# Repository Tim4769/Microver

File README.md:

# Microver

Microver is a compact rover built for the Swiss Rover Challenge. This repository collects the project's electronics, mechanical CAD, software scaffold, PCB test firmware, photos, and shared assets in one place.

## Project

- **Competition:** Swiss Rover Challenge, Switzerland's rover competition for teams of 5 high school students.
- **2025 result:** 3rd place.
- **2026 result:** 1st place.
- **Main disciplines:** electronics, mechanical design, and software.

## Start Here

| Area | Path | Contents |
|---|---|---|
| Electronics | `hardware/final/README.md` | Active PCB revisions, KiCad projects, manufacturing outputs, and validation notes. |
| Mechanical | `mechanical/README.md` | Rover assemblies, wheel pods, chassis parts, mechanisms, mounts, and STEP exports. |
| Software | `software/` | Python rover-control scaffold with camera and control services. |
| PCB test firmware | `hardware/pcb_testing_firmware/README.md` | Arduino sketches and docs for board bring-up and electronics validation. |
| Power diagrams | `hardware/flow_charts/README.md` | Power-system flow charts and supporting diagrams. |

## Current Snapshot

**Electronics**
- Manufacturing-ready PCB work is under `hardware/final/`; archived board spins live under `hardware/archive/`.
- The active stack covers protection Rev B, boost Rev C, buck Rev C, high-side OR-ing Rev A, compute Rev A, and final control Rev A.

**Mechanical**
- Modular CAD lives in `mechanical/assemblies/` and `mechanical/components/`.
- The rover uses field-serviceable wheel pods, aluminium extrusion rails, custom 3D-printed parts, and integrated mounts for electronics, sensors, and mechanisms.

**Software**
- `software/` is the autonomy-ready rover software workspace for control, camera, perception, navigation, and system integration.
- `hardware/pcb_testing_firmware/` contains electronics bring-up and validation sketches only; it is separate from the final software stack.

## Repository Map

- `hardware/` - PCB designs, manufacturing files, archived board revisions, power diagrams, and PCB validation firmware.
- `mechanical/` - CAD assemblies, exported STEP components, manufacturing notes, and mechanical integration references.
- `software/` - Raspberry Pi control software scaffold and future rover software workspace.
- `photos/` - Build, test, and competition photos.
- `logo/` - Current and legacy logo assets.
- `jingle/` - Project audio assets.
- `Microver_presentation_final.pdf` - Final presentation and system overview.

## Maintenance Notes

- Keep generated PCB outputs inside the relevant board revision folder.
- Update CAD references when board dimensions, connector orientation, sensor placement, or mounting details change.
- Keep editable CAD, exported review files, and assembly notes together.
- Keep PCB validation sketches separate from final rover software.
- Update this README when top-level folders move or new subsystem entry points are added.

## License / Contact

All rights reserved. No permission is granted to use, copy, modify, or distribute this repository or its contents without prior written consent. See `LICENSE` for exact terms.

Contact: Tim Wang - timwang007@outlook.com.

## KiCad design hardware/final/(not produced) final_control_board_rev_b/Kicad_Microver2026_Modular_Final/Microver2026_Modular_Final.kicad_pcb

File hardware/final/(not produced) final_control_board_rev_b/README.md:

# Final Control Board - Rev B (Not Produced)

**Revision:** Rev B  
**Production status:** Not produced / not fabricated  
**Project:** Project CK

## Photo
**Note:** Rev B was not produced or fabricated. This photo shows the complete Rev A hardware stack, with every board assembled together—not only the final control board—and is included for visual reference only.

## 1) Overview
This folder contains the KiCad source for an unproduced Rev B update of the Microver 2026 final control board.

The main correction in this KiCad project is that the second motor-driver output net issue from Rev A has been resolved: the connection intended for `OUTA` is no longer tied to the `OUTB` net.

## 2) Important compatibility note
Rev B keeps the same motor-driver stage as Rev A. Because of that, this design is still not compatible with connecting the motor-driver supply directly to the 36 V output from the boost converter.

Do not fabricate or use this design as-is for a 36 V boosted motor rail. If this design is used as the starting point for a future control board, the motor-driver stage should be redesigned with a driver/controller that is suitable for the intended boosted motor voltage. Possible examples include:

- `MP6613`
- `DRV8840`

The final driver selection should be checked against the required motor voltage, current, thermal limits, package, PCB layout constraints, and control-interface requirements before production.

## 3) Files in this folder
- `Kicad_Microver2026_Modular_Final/` - KiCad source project for the unproduced Rev B control board.
- `Photo.JPG` - Complete Rev A board-assembly photo, included only as a visual reference because Rev B was not produced.

Regenerate and review all manufacturing outputs, BOM, CPL, and design-rule checks before considering any future fabrication.

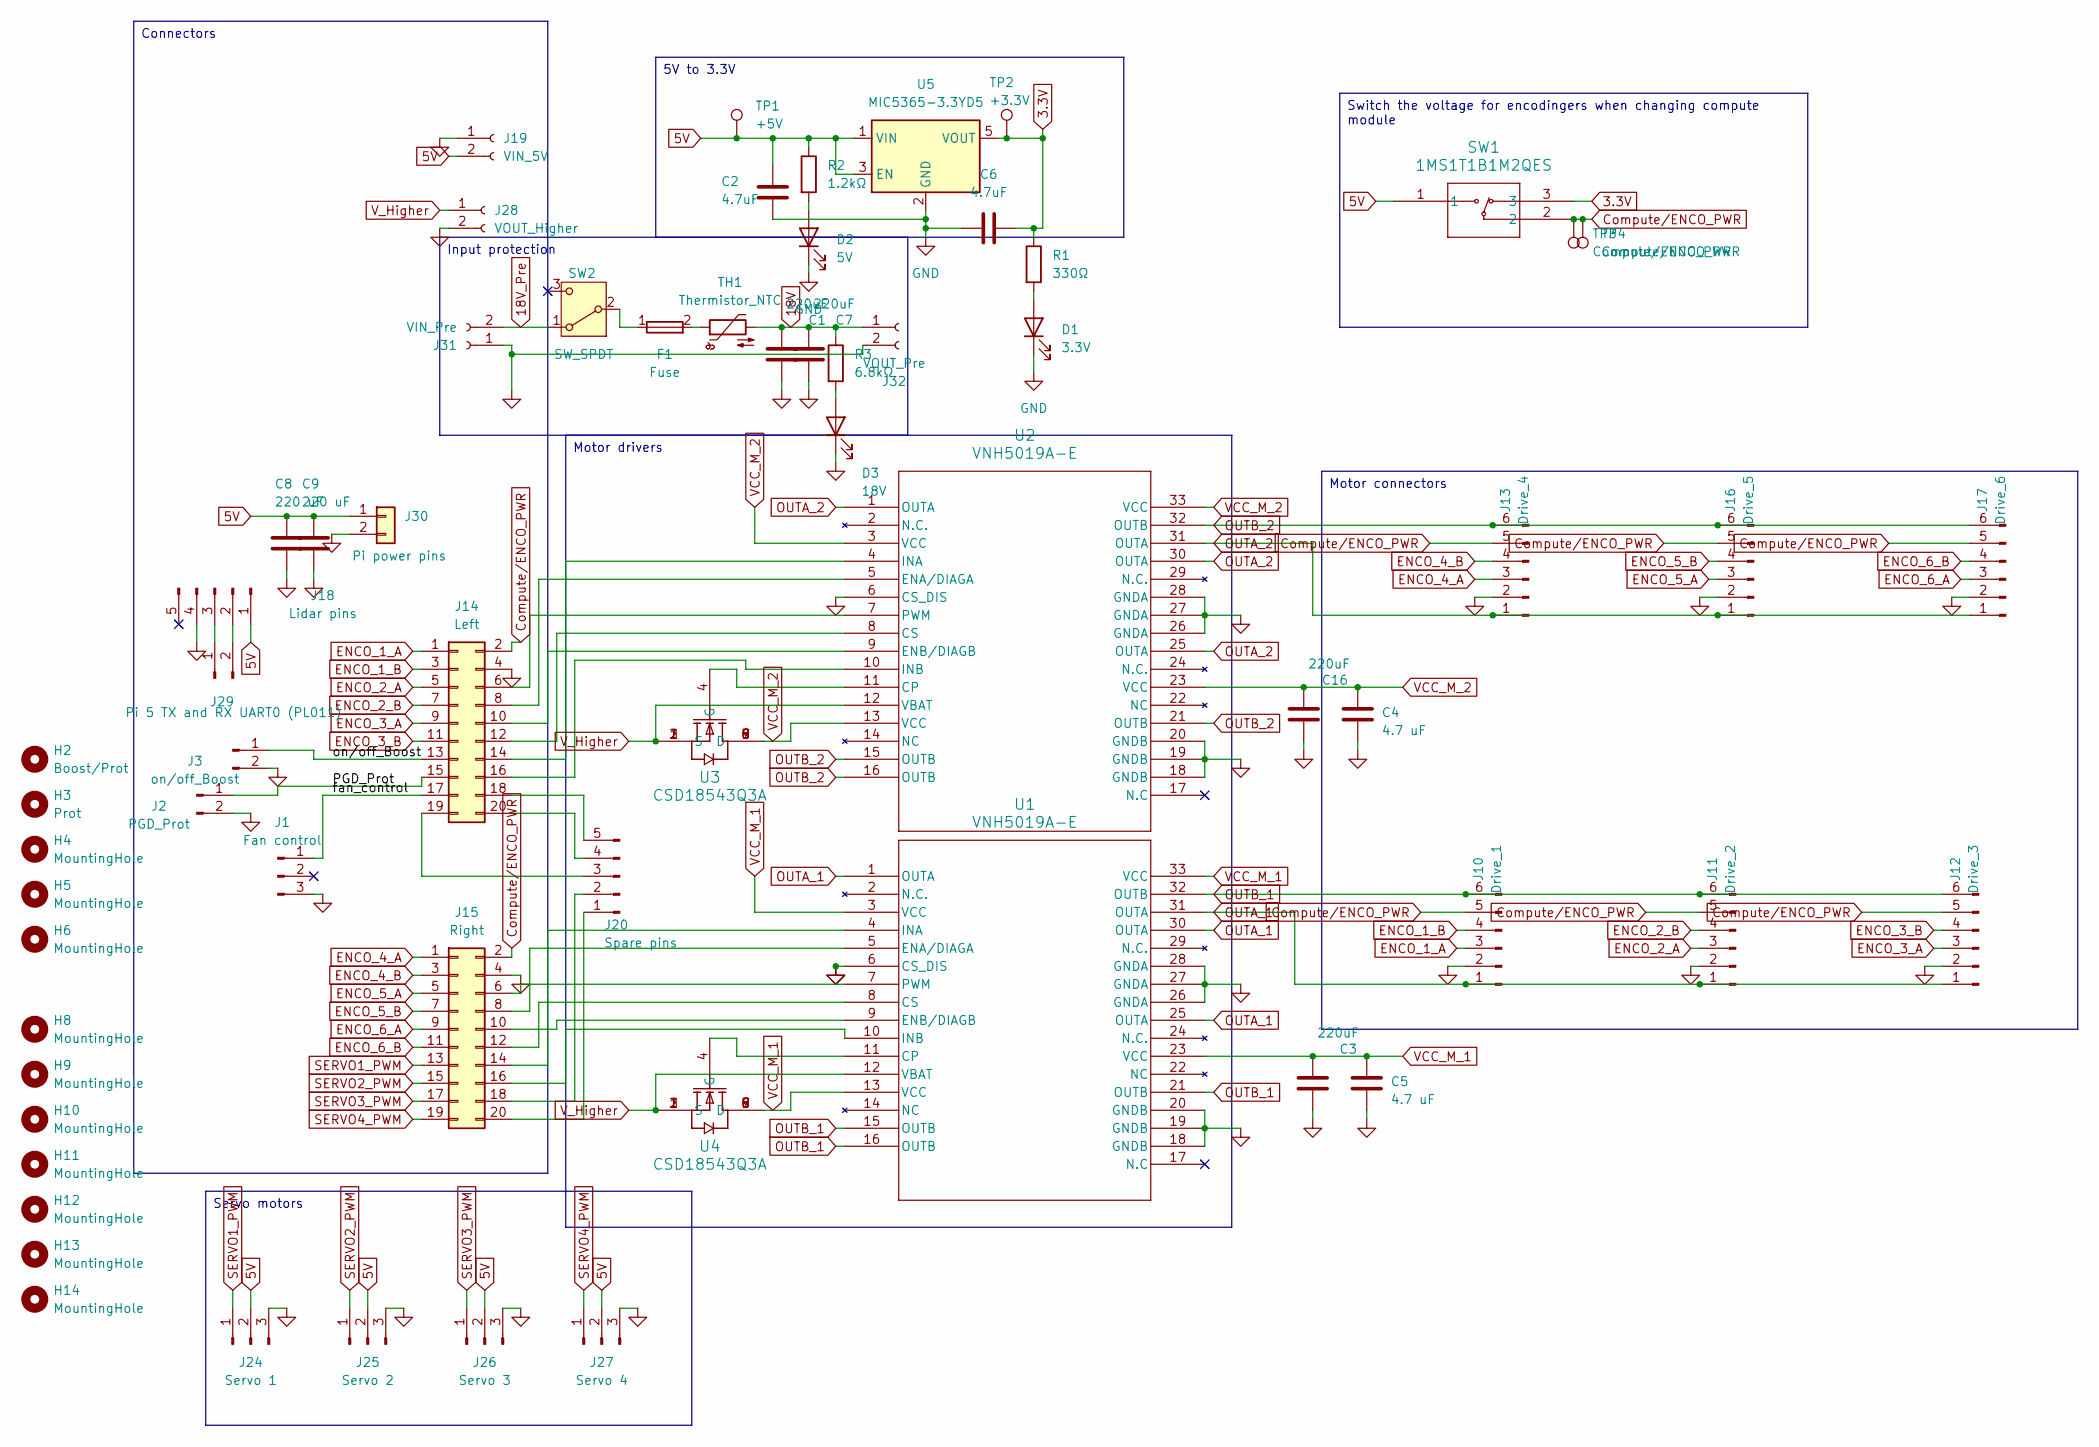
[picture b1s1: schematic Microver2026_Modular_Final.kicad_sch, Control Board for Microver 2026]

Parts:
C1, C3, C7, C16: 220uF; CP_Radial_D8.0mm_P3.50mm; JLCPCB Part Number C106697
C2, C6: 4.7uF; C_0603_1608Metric; JLCPCB Part Number C19666
C4, C5: 4.7 uF; C_1206_3216Metric; JLCPCB Part Number C29823
C8, C9: 220 uF; CP_Elec_4x5.4; JLCPCB Part Number C116389
D1: 3.3V; LED_0603_1608Metric; JLCPCB Part Number C126319
D2: 5V; LED_0603_1608Metric; JLCPCB Part Number C22371297
D3: 18V; LED_0603_1608Metric; JLCPCB Part Number C22371297
F1: Fuse; Fuse PTF-77; JLCPCB Part Number C717030
H2: Boost/Prot; MountingHole_3.2mm_M3
H3: Prot; MountingHole_3.2mm_M3
H4, H5, H6, H8, H9, H10, H11, H12, H13, H14: MountingHole; MountingHole_3.2mm_M3
J1: Fan control; PinHeader_1x03_P2.54mm_Vertical; JLCPCB Part Number C2937625
J2: PGD_Prot; PinHeader_1x02_P2.54mm_Vertical; JLCPCB Part Number C492401
J3: on/off_Boost; PinHeader_1x02_P2.54mm_Vertical; JLCPCB Part Number C492401
J10: Drive_1; JST_PH_B6B-PH-K_1x06_P2.00mm_Vertical
J11: Drive_2; JST_PH_B6B-PH-K_1x06_P2.00mm_Vertical
J12: Drive_3; JST_PH_B6B-PH-K_1x06_P2.00mm_Vertical
J13: Drive_4; JST_PH_B6B-PH-K_1x06_P2.00mm_Vertical
J14: Left; PinHeader_2x10_P2.54mm_Vertical; JLCPCB Part Number C492427
J15: Right; PinHeader_2x10_P2.54mm_Vertical; JLCPCB Part Number C492427
J16: Drive_5; JST_PH_B6B-PH-K_1x06_P2.00mm_Vertical
J17: Drive_6; JST_PH_B6B-PH-K_1x06_P2.00mm_Vertical
J18: Lidar pins; JST_XH_B5B-XH-AM_1x05_P2.50mm_Vertical
J19: VIN_5V; SolderWire-0.75sqmm_1x02_P7mm_D1.25mm_OD3.5mm; JLCPCB Part Number C8269
J20: Spare pins; PinHeader_1x05_P2.54mm_Vertical; JLCPCB Part Number C492404
J24: Servo 1; PinHeader_1x03_P2.54mm_Vertical; JLCPCB Part Number C2937625
J25: Servo 2; PinHeader_1x03_P2.54mm_Vertical; JLCPCB Part Number C2937625
J26: Servo 3; PinHeader_1x03_P2.54mm_Vertical; JLCPCB Part Number C2937625
J27: Servo 4; PinHeader_1x03_P2.54mm_Vertical; JLCPCB Part Number C2937625
J28: VOUT_Higher; SolderWire-0.75sqmm_1x02_P7mm_D1.25mm_OD3.5mm; JLCPCB Part Number C8269
J29: Pi 5 TX and RX UART0 (PL011); PinHeader_1x02_P2.54mm_Vertical; JLCPCB Part Number C492401
J30: Pi power pins; PinHeader_1x02_P2.54mm_Vertical; JLCPCB Part Number C492401
J31: VIN_Pre; TerminalBlock_MaiXu_MX126-5.0-02P_1x02_P5.00mm; JLCPCB Part Number C8269
J32: VOUT_Pre; SolderWire-0.75sqmm_1x02_P7mm_D1.25mm_OD3.5mm; JLCPCB Part Number C8269
R1: 330Ω; R_0603_1608Metric; JLCPCB Part Number C23138
R2: 1.2kΩ; R_0603_1608Metric; JLCPCB Part Number C22765
R3: 6.8kΩ; R_0603_1608Metric; JLCPCB Part Number C23212
SW1: 1MS1T1B1M2QES; SS-12D10G5_XKB; JLCPCB Part Number C319012
SW2: SW_SPDT; SolderWire-0.5sqmm_1x03_P4.8mm_D0.9mm_OD2.3mm
TH1: Thermistor_NTC; NTC thermistor Microver
TP1: +5V; TestPoint_Pad_1.0x1.0mm
TP2: +3.3V; TestPoint_Pad_1.0x1.0mm
TP3, TP4: Compute/ENCO_PWR; TestPoint_Pad_1.0x1.0mm
U1, U2: VNH5019A-E; SOIC_5019A-E_STM; JLCPCB Part Number C2653552
U3, U4: CSD18543Q3A; DNH0008A; JLCPCB Part Number C840100
U5: MIC5365-3.3YD5; SOT-23-5; JLCPCB Part Number C626098

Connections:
3.3V: C6.2, R1.1, SW1.3, TP2.1, U5.5 (VOUT)
5V: C2.1, C8.1, C9.1, J18.1, J19.2, J24.2, J25.2, J26.2, J27.2, J30.1, R2.1, SW1.1, TP1.1, U5.1 (VIN), U5.3 (EN)
18V: C1.1, C7.1, J32.1, R3.1, TH1.2
18V_Pre: J31.2, SW2.1 (A)
/PGD_Prot: J2.1, J14.15 (Pin_8a)
/fan_control: J1.1, J14.17 (Pin_9a)
/on/off_Boost: J3.1, J14.13 (Pin_7a)
Compute/ENCO_PWR: J10.5, J11.5, J12.5, J13.5, J14.2 (Pin_1b), J15.2 (Pin_1b), J16.5, J17.5, SW1.2, TP3.1, TP4.1
ENCO_1_A: J10.3, J14.1 (Pin_1a)
ENCO_1_B: J10.4, J14.3 (Pin_2a)
ENCO_2_A: J11.3, J14.5 (Pin_3a)
ENCO_2_B: J11.4, J14.7 (Pin_4a)
ENCO_3_A: J12.3, J14.9 (Pin_5a)
ENCO_3_B: J12.4, J14.11 (Pin_6a)
ENCO_4_A: J13.3, J15.1 (Pin_1a)
ENCO_4_B: J13.4, J15.3 (Pin_2a)
ENCO_5_A: J15.5 (Pin_3a), J16.3
ENCO_5_B: J15.7 (Pin_4a), J16.4
ENCO_6_A: J15.9 (Pin_5a), J17.3
ENCO_6_B: J15.11 (Pin_6a), J17.4
GND: C1.2, C2.2, C3.2, C4.2, C5.2, C6.1, C7.2, C8.2, C9.2, C16.2, D1.1 (K), D2.1 (K), D3.1 (K), J1.3, J2.2, J3.2, J10.2, J11.2, J12.2, J13.2, J14.4 (Pin_2b), J15.4 (Pin_2b), J16.2, J17.2, J18.4, J19.1, J24.3, J25.3, J26.3, J27.3, J28.2, J30.2, J31.1, J32.2, U1.6 (CS_DIS), U1.18 (GNDB), U1.19 (GNDB), U1.20 (GNDB), U1.26 (GNDA), U1.27 (GNDA), U1.28 (GNDA), U2.6 (CS_DIS), U2.18 (GNDB), U2.19 (GNDB), U2.20 (GNDB), U2.26 (GNDA), U2.27 (GNDA), U2.28 (GNDA), U5.2 (GND)
unnamed: D1.2 (A), R1.2
unnamed: D2.2 (A), R2.2
unnamed: D3.2 (A), R3.2
unnamed: F1.2, TH1.1
unnamed: J14.6 (Pin_3b), U2.7 (PWM)
unnamed: J14.8 (Pin_4b), U2.5 (ENA/DIAGA)
unnamed: J14.10 (Pin_5b), U2.9 (ENB/DIAGB)
unnamed: J14.12 (Pin_6b), U2.8 (CS)
unnamed: J14.14 (Pin_7b), U2.4 (INA)
unnamed: J14.16 (Pin_8b), U2.10 (INB)
unnamed: J14.18 (Pin_9b), J20.5
unnamed: J14.19 (Pin_10a), J20.3
unnamed: J14.20 (Pin_10b), J20.4
unnamed: J15.6 (Pin_3b), U1.7 (PWM)
unnamed: J15.8 (Pin_4b), U1.5 (ENA/DIAGA)
unnamed: J15.10 (Pin_5b), U1.9 (ENB/DIAGB)
unnamed: J15.12 (Pin_6b), U1.8 (CS)
unnamed: J15.14 (Pin_7b), U1.4 (INA)
unnamed: J15.16 (Pin_8b), U1.10 (INB)
unnamed: J15.18 (Pin_9b), J20.2
unnamed: J15.20 (Pin_10b), J20.1
unnamed: J18.2, J29.2
unnamed: J18.3, J29.1
unnamed: F1.1, SW2.2 (B)
unnamed: U1.11 (CP), U4.4 (G)
unnamed: U2.11 (CP), U3.4 (G)
OUTA_1: J10.1, J11.1, J12.1, U1.1 (OUTA), U1.25 (OUTA), U1.30 (OUTA), U1.31 (OUTA)
OUTA_2: J13.1, J16.1, J17.1, U2.1 (OUTA), U2.25 (OUTA), U2.30 (OUTA), U2.31 (OUTA)
OUTB_1: J10.6, J11.6, J12.6, U1.15 (OUTB), U1.16 (OUTB), U1.21 (OUTB), U1.32 (OUTB)
OUTB_2: J13.6, J16.6, J17.6, U2.15 (OUTB), U2.16 (OUTB), U2.21 (OUTB), U2.32 (OUTB)
SERVO1_PWM: J15.13 (Pin_7a), J24.1
SERVO2_PWM: J15.15 (Pin_8a), J25.1
SERVO3_PWM: J15.17 (Pin_9a), J26.1
SERVO4_PWM: J15.19 (Pin_10a), J27.1
VCC_M_1: C3.1, C5.1, U1.3 (VCC), U1.13 (VCC), U1.23 (VCC), U1.33 (VCC), U4.5 (D), U4.6 (D), U4.7 (D), U4.8 (D), U4.9 (D)
VCC_M_2: C4.1, C16.1, U2.3 (VCC), U2.13 (VCC), U2.23 (VCC), U2.33 (VCC), U3.5 (D), U3.6 (D), U3.7 (D), U3.8 (D), U3.9 (D)
V_Higher: J28.1, U1.12 (VBAT), U2.12 (VBAT), U3.1 (S), U3.2 (S), U3.3 (S), U4.1 (S), U4.2 (S), U4.3 (S)

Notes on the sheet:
Motor drivers
Input protection
Servo motors
Motor connectors
5V to 3.3V
Switch the voltage for encodingers when changing compute module
Connectors

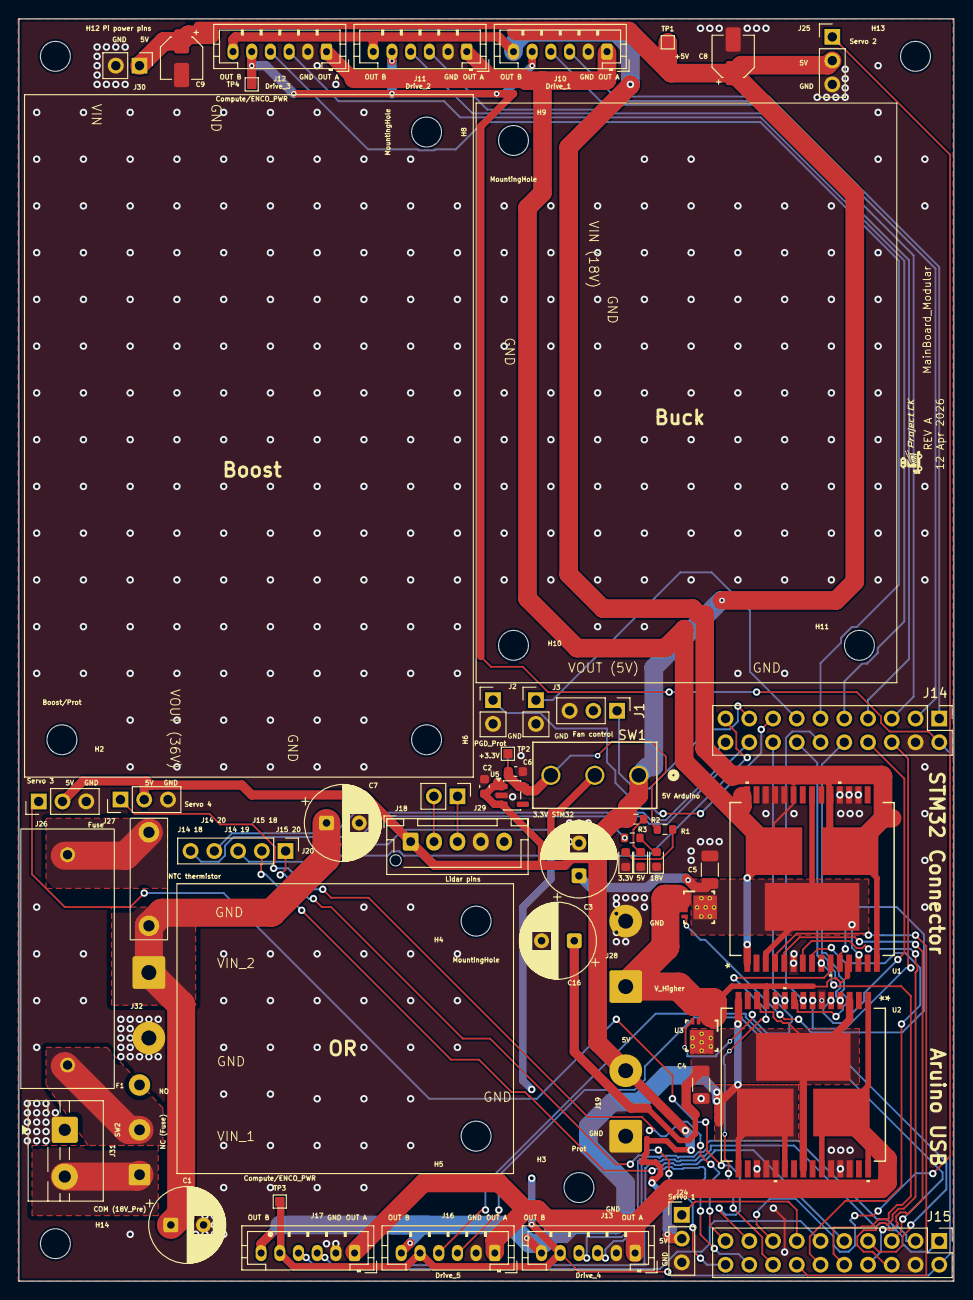
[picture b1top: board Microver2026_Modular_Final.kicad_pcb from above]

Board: 4 copper layers, 100.0 x 135.0 mm, 64 parts (0 on the bottom side), 58 nets.

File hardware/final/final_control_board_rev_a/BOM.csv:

"Reference","Qty","Value","Exclude from BOM","Footprint","JLCPCB Part Number"
"C1,C3,C7,C16","4","220uF","","Capacitor_THT:CP_Radial_D8.0mm_P3.50mm","C106697"
"C2,C6","2","4.7uF","","Capacitor_SMD:C_0603_1608Metric","C19666"
"C4,C5","2","4.7 uF","","Capacitor_SMD:C_1206_3216Metric","C29823"
"C8,C9","2","220 uF","","Capacitor_SMD:CP_Elec_4x5.4","C116389"
"D1","1","3.3V","","LED_SMD:LED_0603_1608Metric","C126319"
"D2","1","5V","","LED_SMD:LED_0603_1608Metric","C22371297"
"D3","1","18V","","LED_SMD:LED_0603_1608Metric","C22371297"
"F1","1","Fuse","","microver footprint Library:Fuse PTF-77","C717030"
"H2","1","Boost/Prot","Excluded from BOM","MountingHole:MountingHole_3.2mm_M3",""
"H3","1","Prot","Excluded from BOM","MountingHole:MountingHole_3.2mm_M3",""
"H4,H5,H6,H8,H9,H10,H11,H12,H13,H14","10","MountingHole","Excluded from BOM","MountingHole:MountingHole_3.2mm_M3",""
"J1","1","Fan control","","Connector_PinHeader_2.54mm:PinHeader_1x03_P2.54mm_Vertical","C2937625"
"J2","1","PGD_Prot","","Connector_PinHeader_2.54mm:PinHeader_1x02_P2.54mm_Vertical","C492401"
"J3","1","on/off_Boost","","Connector_PinHeader_2.54mm:PinHeader_1x02_P2.54mm_Vertical","C492401"
"J10","1","Drive_1","","Connector_JST:JST_PH_B6B-PH-K_1x06_P2.00mm_Vertical",""
"J11","1","Drive_2","","Connector_JST:JST_PH_B6B-PH-K_1x06_P2.00mm_Vertical",""
"J12","1","Drive_3","","Connector_JST:JST_PH_B6B-PH-K_1x06_P2.00mm_Vertical",""
"J13","1","Drive_4","","Connector_JST:JST_PH_B6B-PH-K_1x06_P2.00mm_Vertical",""
"J14","1","Left","","Connector_PinHeader_2.54mm:PinHeader_2x10_P2.54mm_Vertical","C492427"
"J15","1","Right","","Connector_PinHeader_2.54mm:PinHeader_2x10_P2.54mm_Vertical","C492427"
"J16","1","Drive_5","","Connector_JST:JST_PH_B6B-PH-K_1x06_P2.00mm_Vertical",""
"J17","1","Drive_6","","Connector_JST:JST_PH_B6B-PH-K_1x06_P2.00mm_Vertical",""
"J18","1","Lidar pins","","Connector_JST:JST_XH_B5B-XH-AM_1x05_P2.50mm_Vertical",""
"J19","1","VIN_5V","","Connector_Wire:SolderWire-0.75sqmm_1x02_P7mm_D1.25mm_OD3.5mm","C8269"
"J20","1","Spare pins","","Connector_PinHeader_2.54mm:PinHeader_1x05_P2.54mm_Vertical","C492404"
"J24","1","Servo 1","","Connector_PinHeader_2.54mm:PinHeader_1x03_P2.54mm_Vertical","C2937625"
"J25","1","Servo 2","","Connector_PinHeader_2.54mm:PinHeader_1x03_P2.54mm_Vertical","C2937625"
"J26","1","Servo 3","","Connector_PinHeader_2.54mm:PinHeader_1x03_P2.54mm_Vertical","C2937625"
"J27","1","Servo 4","","Connector_PinHeader_2.54mm:PinHeader_1x03_P2.54mm_Vertical","C2937625"
"J28","1","VOUT_Higher","","Connector_Wire:SolderWire-0.75sqmm_1x02_P7mm_D1.25mm_OD3.5mm","C8269"
"J29","1","Pi 5 TX and RX UART0 (PL011)","","Connector_PinHeader_2.54mm:PinHeader_1x02_P2.54mm_Vertical","C492401"
"J30","1","Pi power pins","","Connector_PinHeader_2.54mm:PinHeader_1x02_P2.54mm_Vertical","C492401"
"J31","1","VIN_Pre","","TerminalBlock:TerminalBlock_MaiXu_MX126-5.0-02P_1x02_P5.00mm","C8269"
"J32","1","VOUT_Pre","","Connector_Wire:SolderWire-0.75sqmm_1x02_P7mm_D1.25mm_OD3.5mm","C8269"
"R1","1","330Ω","","Resistor_SMD:R_0603_1608Metric","C23138"
"R2","1","1.2kΩ","","Resistor_SMD:R_0603_1608Metric","C22765"
"R3","1","6.8kΩ","","Resistor_SMD:R_0603_1608Metric","C23212"
"SW1","1","1MS1T1B1M2QES","","Microver2026_Modular_Footprint:SS-12D10G5_XKB","C319012"
"SW2","1","SW_SPDT","","Connector_Wire:SolderWire-0.5sqmm_1x03_P4.8mm_D0.9mm_OD2.3mm",""
"TH1","1","Thermistor_NTC","Excluded from BOM","microver footprint Library:NTC thermistor Microver",""
"TP1","1","+5V","Excluded from BOM","TestPoint:TestPoint_Pad_1.0x1.0mm",""
"TP2","1","+3.3V","Excluded from BOM","TestPoint:TestPoint_Pad_1.0x1.0mm",""
"TP3,TP4","2","Compute/ENCO_PWR","Excluded from BOM","TestPoint:TestPoint_Pad_1.0x1.0mm",""
"U1,U2","2","VNH5019A-E","","Buck_Footprint_Library:SOIC_5019A-E_STM","C2653552"
"U3,U4","2","CSD18543Q3A","","Buck_Footprint_Library:DNH0008A","C840100"
"U5","1","MIC5365-3.3YD5","","Package_TO_SOT_SMD:SOT-23-5","C626098"

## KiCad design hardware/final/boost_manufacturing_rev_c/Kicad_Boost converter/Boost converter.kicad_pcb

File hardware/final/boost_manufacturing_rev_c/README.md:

# Boost Converter (LM5122-Q1) — Rev C

**Owner / Contact:** Tim Wang — timwang007@outlook.com  
**Revision:** Rev C  
**Date:** 2026-04-13  
**Project:** Project CK  

## Photo

## 1) Scope
Rev C is the next active boost-converter spin for the LM5122-Q1 power stage. It carries forward the Rev B architecture and prior value/layout updates, then adds more MOSFET capacity on both switching sides plus per-gate damping so the board can handle higher current with better current sharing and switching control.

## 2) PCB stack-up (applies to all Rev C boards)
- Layer stack:
  - F.Silkscreen (top silk screen), color/material not specified
  - F.Paste (top solder paste)
  - F.Mask (top solder mask), thickness 0.01 mm, color not specified, material not specified, Er 3.3, LossTg 0
  - F.Cu 0.035 mm
  - Dielectric 1 (prepreg) 0.10 mm FR4, Er 4.5, LossTg 0.02
  - In1.Cu 0.017 mm
  - Dielectric 2 (core) 1.25 mm FR4, Er 4.5, LossTg 0.02
  - In2.Cu 0.017 mm
  - Dielectric 3 (prepreg) 0.10 mm FR4, Er 4.5, LossTg 0.02
  - B.Cu 0.035 mm
  - B.Mask (bottom solder mask) 0.035 mm, color not specified, material not specified, Er 3.3, LossTg 0
  - B.Paste (bottom solder paste)
  - B.Silkscreen (bottom silk screen), color/material not specified
  - Finish: HAL lead-free

## 3) Change Summary
### Carryover from Rev B
- Rev B LM5122-Q1 architecture, value corrections, and prior EMI/layout cleanup are carried forward unless superseded here.
- Rev B soft-start shutdown control through the `SS` pin remains in place.
- Rev B mechanical/layout additions such as mounting holes, external-signal GND reference, Kelvin sense routing, and return-via cleanup remain part of the design baseline.

### Power stage updates
- Added one extra MOSFET in parallel on the high-side path to increase current capability and reduce per-device stress.
- Added one extra MOSFET in parallel on the low-side path to increase current capability and improve current sharing in the synchronous path.
- Added `2 Ohm` gate resistors for each MOSFET gate to damp ringing and improve switching control with the expanded MOSFET bank.

### Bring-up / validation focus
- Re-check gate-drive timing, switching-node ringing, and dead-time behavior with the added parallel MOSFETs before releasing fabrication data.
- Re-verify thermal rise and current sharing across the high-side and low-side MOSFET groups at the intended higher load current.

## 4) Reference Notes
- Use `hardware/archive/boost_manufacturing_rev_b/README.md` for the Rev B baseline and prior component/layout changes.
- Use `hardware/archive/boost_manufacturing_rev_a/README.md` for the original architecture, operating targets, and bring-up context.

## 5) Files
- `Boost converter_3D.step` — 3D STEP model of the assembled PCB.
- Rev C BOM/CPL/Gerbers have not been regenerated yet. Regenerate all manufacturing outputs after the Rev C KiCad design is finalized.
- This folder currently holds the Rev C documentation entry so the active hardware naming and README format stay aligned with the rest of `hardware/final/`.

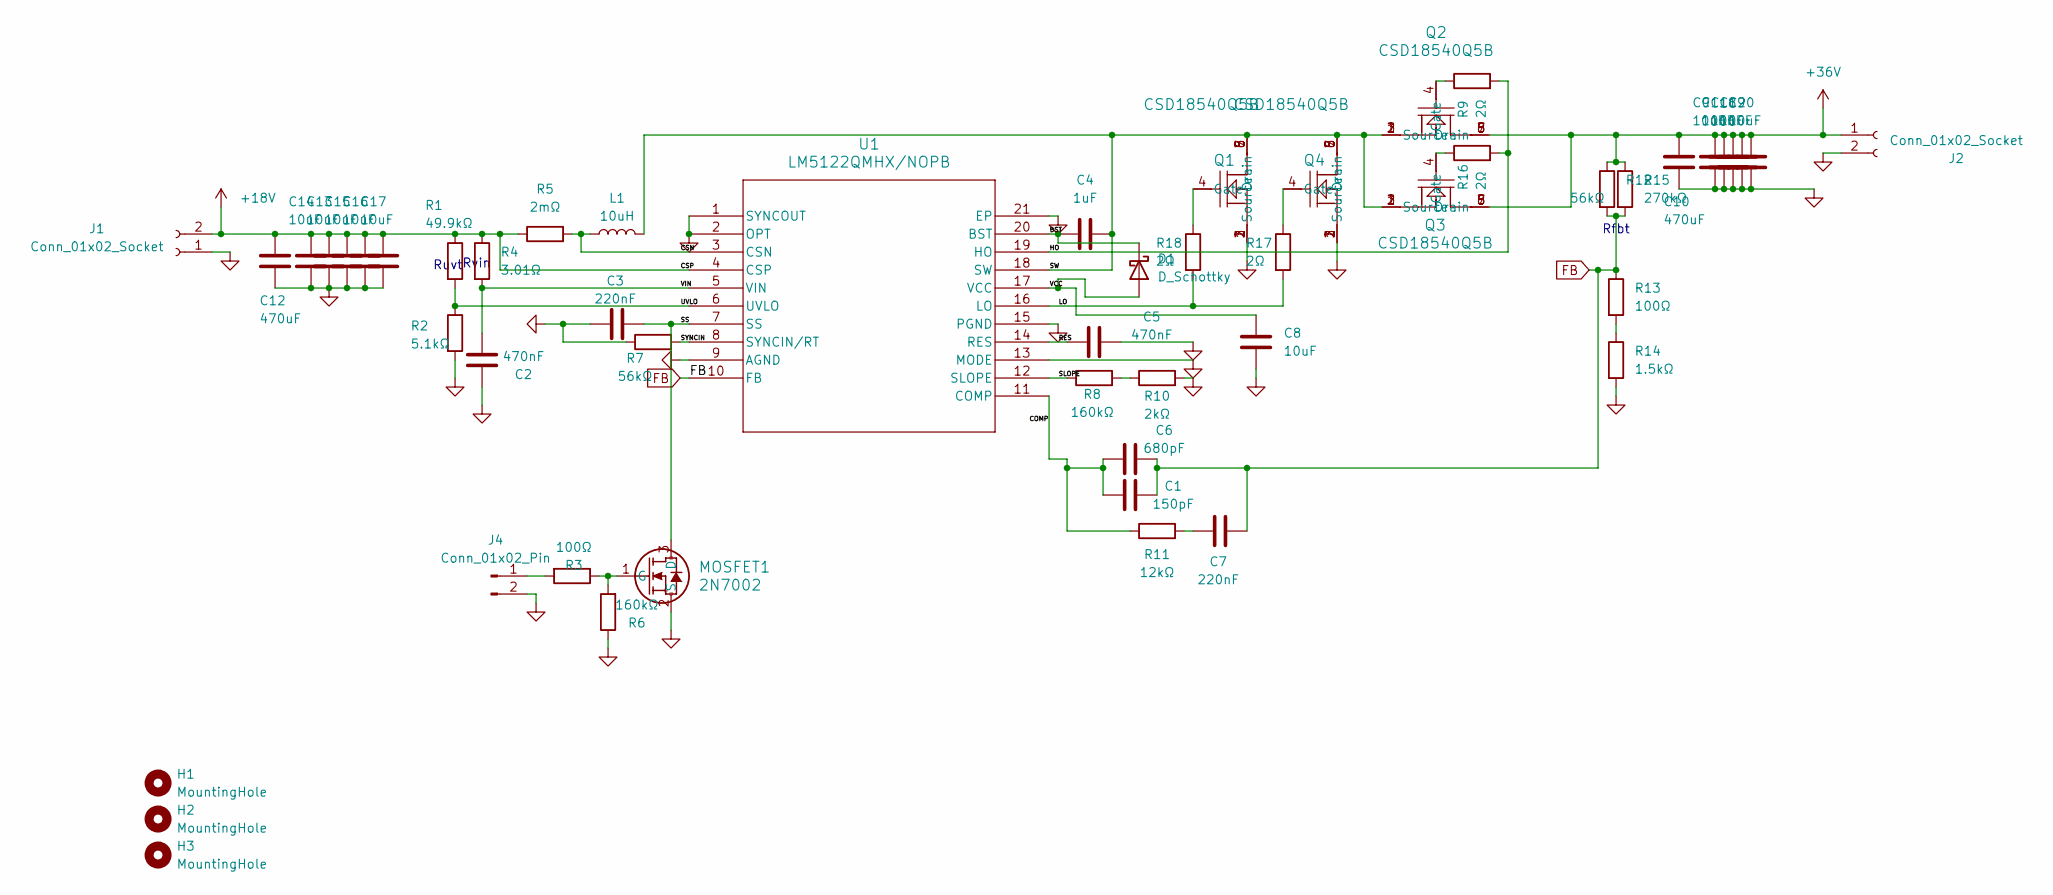
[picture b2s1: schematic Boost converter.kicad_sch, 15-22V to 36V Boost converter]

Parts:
C1: 150pF; C_0603_1608Metric; JLCPCB Part number C1594
C2: 470nF; C_0805_2012Metric; JLCPCB Part number C13967
C3: 220nF; C_0603_1608Metric; JLCPCB Part number C21120
C4: 1uF; C_0805_2012Metric; JLCPCB Part number C28323
C5: 470nF; C_0603_1608Metric; JLCPCB Part number C1623
C6: 680pF; C_0603_1608Metric; JLCPCB Part number C1630
C7: 220nF; C_0805_2012Metric; JLCPCB Part number C5378
C8, C9, C11, C13, C14, C15, C16, C17, C18, C19, C20: 10uF; C_0805_2012Metric; JLCPCB Part number C440198
C10, C12: 470uF; CP_Radial_D10.0mm_P5.00mm; JLCPCB Part number C5438877
D1: D_Schottky; D_SMA; JLCPCB Part number C18199198
H1, H2, H3: MountingHole; MountingHole_3.2mm_M3
J1, J2: Conn_01x02_Socket; TerminalBlock_MetzConnect_Type055_RT01502HDWU_1x02_P5.00mm_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
J4: Conn_01x02_Pin; PinHeader_1x02_P2.54mm_Vertical
L1: 10uH; IND_SER2918H_COC; JLCPCB Part number C3037600
MOSFET1: 2N7002; SOT-23TO-236_318-08_ONS; JLCPCB Part number C8545
Q1, Q2, Q3, Q4: CSD18540Q5B; DNK0008A; JLCPCB Part number C86513
R1: 49.9kΩ; R_0603_1608Metric; JLCPCB Part number C23184
R2: 5.1kΩ; R_0603_1608Metric; JLCPCB Part number C23186
R3, R13: 100Ω; R_0603_1608Metric; JLCPCB Part number C22775
R4: 3.01Ω; R_0603_1608Metric; JLCPCB Part number C49655781
R5: 2mΩ; R_2512_6332Metric; JLCPCB Part number C728306
R6, R8: 160kΩ; R_0603_1608Metric; JLCPCB Part number C22813
R7, R12: 56kΩ; R_0603_1608Metric; JLCPCB Part number C23206
R9, R16, R17, R18: 2Ω; R_0603_1608Metric; JLCPCB Part number C22977
R10: 2kΩ; R_0603_1608Metric; JLCPCB Part number C22975
R11: 12kΩ; R_0603_1608Metric; JLCPCB Part number C22790
R14: 1.5kΩ; R_0603_1608Metric; JLCPCB Part number C22843
R15: 270kΩ; R_0603_1608Metric; JLCPCB Part number C22965
U1: LM5122QMHX/NOPB; HTSSOP20; JLCPCB Part number C527477

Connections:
+18V: C12.1, C13.1, C14.1, C15.1, C16.1, C17.1, J1.2, R1.1, R4.1, R5.1, U1.4 (CSP)
+36V: C9.1, C10.1, C11.1, C18.1, C19.1, C20.1, J2.1, Q2.5 (Drain), Q2.6 (Drain), Q2.7 (Drain), Q2.8 (Drain), Q3.5 (Drain), Q3.6 (Drain), Q3.7 (Drain), Q3.8 (Drain), R12.1, R15.1
/BST: C4.1, D1.1 (K), U1.20 (BST)
/COMP: C1.1, C6.1, R11.1, U1.11 (COMP)
/CSN: L1.1, R5.2, U1.3 (CSN)
/HO: R9.2, R16.2, U1.19 (HO)
/LO: R17.2, R18.2, U1.16 (LO)
/RES: C5.1, U1.14 (RES)
/SLOPE: R8.1, U1.12 (SLOPE)
/SS: C3.2, MOSFET1.3 (D), U1.7 (SS)
/SW: C4.2, L1.2, Q1.5 (Drain), Q1.6 (Drain), Q1.7 (Drain), Q1.8 (Drain), Q2.1 (Source), Q2.2 (Source), Q2.3 (Source), Q3.1 (Source), Q3.2 (Source), Q3.3 (Source), Q4.5 (Drain), Q4.6 (Drain), Q4.7 (Drain), Q4.8 (Drain), U1.18 (SW)
/SYNCIN: R7.2, U1.8 (SYNCIN/RT)
/UVLO: R1.2, R2.1, U1.6 (UVLO)
/VCC: C8.1, D1.2 (A), U1.17 (VCC)
/VIN: C2.2, R4.2, U1.5 (VIN)
FB: C1.2, C6.2, C7.2, R12.2, R13.1, R15.2, U1.10 (FB)
GND: C2.1, C3.1, C5.2, C8.2, C9.2, C10.2, C11.2, C12.2, C13.2, C14.2, C15.2, C16.2, C17.2, C18.2, C19.2, C20.2, J1.1, J2.2, J4.2, MOSFET1.2 (S), Q1.1 (Source), Q1.2 (Source), Q1.3 (Source), Q4.1 (Source), Q4.2 (Source), Q4.3 (Source), R2.2, R6.1, R7.1, R10.2, R14.2, U1.1 (SYNCOUT), U1.2 (OPT), U1.9 (AGND), U1.13 (MODE), U1.15 (PGND), U1.21 (EP)
unnamed: C7.1, R11.2
unnamed: J4.1, R3.2
unnamed: MOSFET1.1 (G), R3.1, R6.2
unnamed: Q1.4 (Gate), R18.1
unnamed: Q2.4 (Gate), R9.1
unnamed: Q3.4 (Gate), R16.1
unnamed: Q4.4 (Gate), R17.1
unnamed: R8.2, R10.1
unnamed: R13.2, R14.1

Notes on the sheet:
Rvin
Ruvt
Rfbt

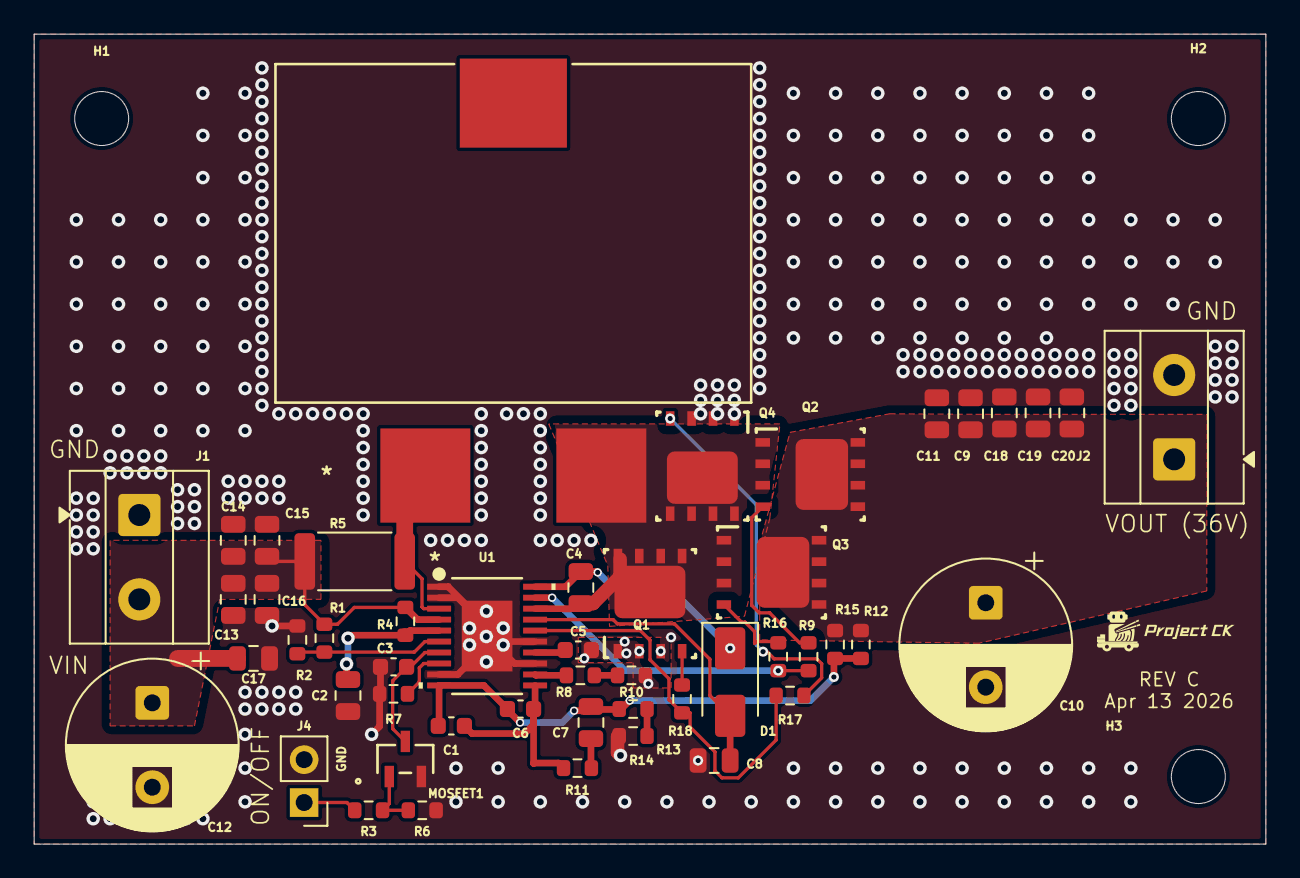
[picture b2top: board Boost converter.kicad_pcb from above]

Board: 4 copper layers, 73.0 x 48.0 mm, 52 parts (0 on the bottom side), 26 nets.

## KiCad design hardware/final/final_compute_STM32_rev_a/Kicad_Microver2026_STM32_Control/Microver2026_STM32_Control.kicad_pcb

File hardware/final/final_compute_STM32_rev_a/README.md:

# Final Compute Board STM32 - Rev A

- **Owner / Contact:** Tim Wang - timwang007@outlook.com
- **Revision:** Rev A
- **Project:** Project CK

## Photo

## 1) Overview
Rev A is the STM32 compute-board option for the Microver 2026 final hardware stack. The KiCad project is titled `Compute unit STM32G4RCT6` and uses the same `Left` / `Right` board-to-board header concept as the final control board.

## 2) Major interfaces
- `J14` - `Left` compute/control interconnect.
- `J15` - `Right` compute/control interconnect.
- Main MCU footprint/library target: STM32G4 control MCU in LQFP64 package.

Mate this board only after confirming `J14` and `J15` orientation against `../final_control_board_rev_a/`.

## 3) Files in this folder
- `BOM.csv` - Rev A bill of materials.
- `CPL.csv` - Rev A centroid / pick-and-place file.
- `Gerber/` and `Gerber.zip` - Rev A fabrication outputs.
- `Kicad_Microver2026_STM32_Control/` - KiCad source project and local libraries.
- `Microver2026_STM32_Control_3D.step` - 3D STEP model of the assembled PCB.
- `Photo.JPG` - Board photo/reference image.

## 4) Bring-up notes
- Bring up on a current-limited supply before connecting downstream loads.
- Verify the compute/control interconnect orientation before mating with the final control board.
- Regenerate BOM, CPL, Gerbers, and the zipped Gerber package after any KiCad edit.

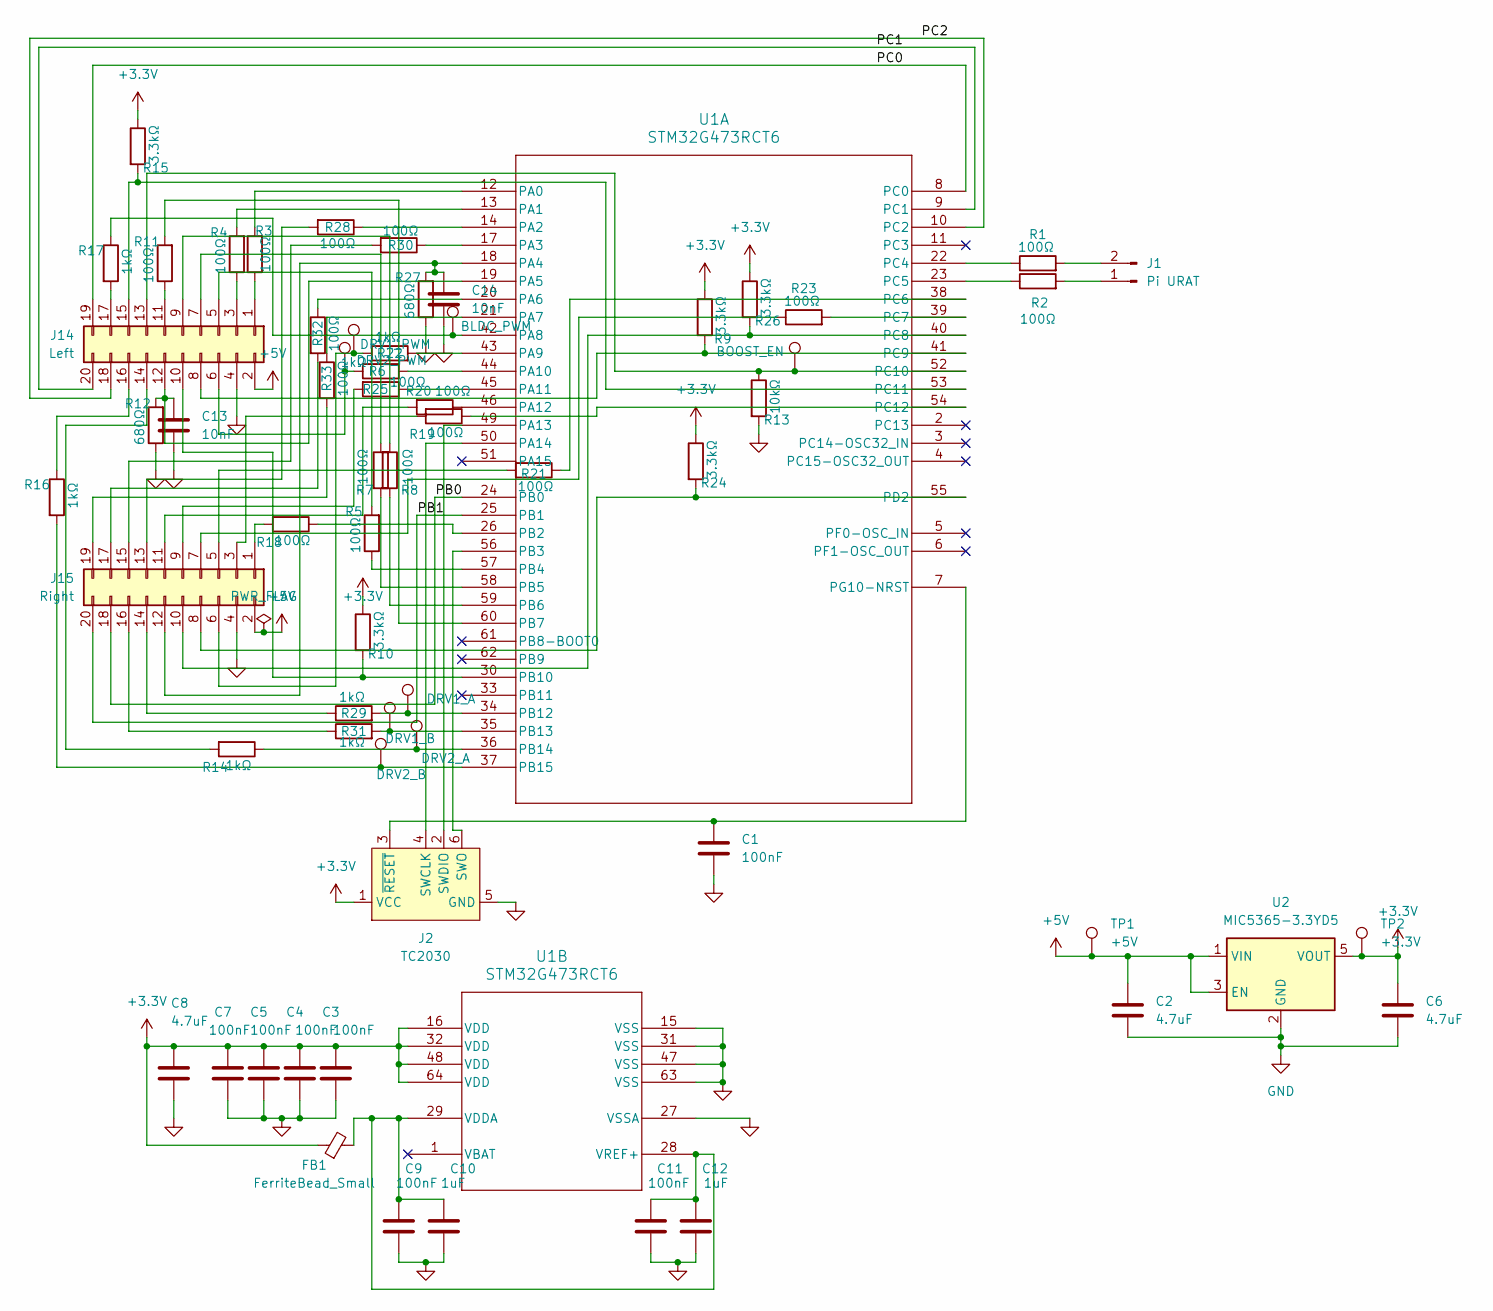
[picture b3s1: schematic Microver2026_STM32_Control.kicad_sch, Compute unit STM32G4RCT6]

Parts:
C1, C3, C4, C5, C7, C9, C11: 100nF; C_0603_1608Metric; JLCPCB part number C14663
C2, C6, C8: 4.7uF; C_0603_1608Metric; JLCPCB part number C19666
C10, C12: 1uF; C_0603_1608Metric; JLCPCB part number C15849
C13, C14: 10nF; C_0603_1608Metric; JLCPCB part number C57112
FB1: FerriteBead_Small; R_0603_1608Metric; JLCPCB part number C14709
J1: Pi URAT; PinHeader_1x02_P2.54mm_Vertical; JLCPCB part number C492401
J2: TC2030; Tag-Connect_TC2030-IDC-FP_2x03_P1.27mm_Vertical
J14: Left; PinHeader_2x10_P2.54mm_Vertical
J15: Right; PinHeader_2x10_P2.54mm_Vertical
R1, R2, R3, R4, R5, R7, R8, R11, R18, R19, R20, R21, R23, R25, R28, R30, R32, R33: 100Ω; R_0603_1608Metric; JLCPCB part number C22775
R6, R14, R16, R17, R22, R29, R31: 1kΩ; R_0603_1608Metric; JLCPCB part number C21190
R9, R10, R15, R24, R26: 3.3kΩ; R_0603_1608Metric; JLCPCB part number C22978
R12, R27: 680Ω; R_0603_1608Metric; JLCPCB part number C23228
R13: 10kΩ; R_0603_1608Metric; JLCPCB part number C25804
TP1: +5V; TestPoint_Pad_1.0x1.0mm
TP2: +3.3V; TestPoint_Pad_1.0x1.0mm
TP3: BLDC_PWM; TestPoint_Pad_1.0x1.0mm
TP4: DRV1_A; TestPoint_Pad_1.0x1.0mm
TP5: DRV1_B; TestPoint_Pad_1.0x1.0mm
TP6: DRV2_A; TestPoint_Pad_1.0x1.0mm
TP7: DRV1_PWM; TestPoint_Pad_1.0x1.0mm
TP8: DRV2_B; TestPoint_Pad_1.0x1.0mm
TP12: DRV2_PWM; TestPoint_Pad_1.0x1.0mm
TP15: BOOST_EN; TestPoint_Pad_1.0x1.0mm
U1: STM32G473RCT6; LQFP64-10x10mm; JLCPCB part number C529361
U2: MIC5365-3.3YD5; SOT-23-5; JLCPCB part number C626098

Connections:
+3.3V: C3.1, C4.1, C5.1, C6.1, C7.1, C8.1, FB1.1, J2.1 (VCC), R9.1, R10.1, R15.1, R24.1, R26.1, TP2.1, U1.16 (VDD), U1.32 (VDD), U1.48 (VDD), U1.64 (VDD), U2.5 (VOUT)
+5V: C2.1, J14.2 (Pin_1b), J15.2 (Pin_1b), TP1.1, U2.1 (VIN), U2.3 (EN)
/PB0: J15.18 (Pin_9b), U1.24 (PB0)
/PB1: J15.20 (Pin_10b), U1.25 (PB1)
/PC0: J14.19 (Pin_10a), U1.8 (PC0)
/PC1: J14.20 (Pin_10b), U1.9 (PC1)
/PC2: J14.18 (Pin_9b), U1.10 (PC2)
GND: C1.2, C2.2, C3.2, C4.2, C5.2, C6.2, C7.2, C8.2, C9.2, C10.2, C11.2, C12.2, C13.2, C14.2, J2.5 (GND), J14.4 (Pin_2b), J15.4 (Pin_2b), R12.1, R13.2, R27.1, U1.15 (VSS), U1.27 (VSSA), U1.31 (VSS), U1.47 (VSS), U1.63 (VSS), U2.2 (GND)
unnamed: J1.1, R2.2
unnamed: J1.2, R1.2
unnamed: J2.4 (SWCLK), U1.50 (PA14)
unnamed: J2.2 (SWDIO), U1.49 (PA13)
unnamed: J2.6 (SWO), U1.56 (PB3)
unnamed: C1.1, J2.3 (~RESET), U1.7 (PG10-NRST)
unnamed: J14.1 (Pin_1a), R3.1
unnamed: J14.3 (Pin_2a), R4.1
unnamed: J14.5 (Pin_3a), R5.2
unnamed: J14.6 (Pin_3b), R6.2, TP12.1
unnamed: J14.7 (Pin_4a), R7.1
unnamed: J14.8 (Pin_4b), R9.2, U1.41 (PC9)
unnamed: J14.9 (Pin_5a), R8.1
unnamed: J14.10 (Pin_5b), R10.2, U1.30 (PB10)
unnamed: J14.11 (Pin_6a), R11.1
unnamed: C13.1, J14.12 (Pin_6b), R12.2, U1.19 (PA5)
unnamed: J14.13 (Pin_7a), R13.1, TP15.1, U1.52 (PC10)
unnamed: J14.14 (Pin_7b), R14.2
unnamed: J14.15 (Pin_8a), R15.2, U1.53 (PC11)
unnamed: J14.16 (Pin_8b), R16.1
unnamed: J14.17 (Pin_9a), R17.2
unnamed: J15.1 (Pin_1a), R18.2
unnamed: J15.3 (Pin_2a), R19.2
unnamed: J15.5 (Pin_3a), R21.2
unnamed: J15.6 (Pin_3b), R22.1, TP7.1
unnamed: J15.7 (Pin_4a), R23.1
unnamed: J15.8 (Pin_4b), R24.2, U1.55 (PD2)
unnamed: J15.9 (Pin_5a), R25.2
unnamed: J15.10 (Pin_5b), R26.2, U1.40 (PC8)
unnamed: J15.11 (Pin_6a), R20.2
unnamed: C14.1, J15.12 (Pin_6b), R27.2, U1.18 (PA4)
unnamed: J15.13 (Pin_7a), R28.2
unnamed: J15.14 (Pin_7b), R29.1
unnamed: J15.15 (Pin_8a), R30.2
unnamed: J15.16 (Pin_8b), R31.1
unnamed: J15.17 (Pin_9a), R32.2
unnamed: J15.19 (Pin_10a), R33.2
unnamed: R3.2, U1.12 (PA0)
unnamed: R4.2, U1.13 (PA1)
unnamed: R28.1, U1.14 (PA2)
unnamed: R30.1, U1.17 (PA3)
unnamed: R32.1, U1.20 (PA6)
unnamed: R33.1, U1.21 (PA7)
unnamed: R17.1, TP3.1, U1.42 (PA8)
unnamed: R22.2, U1.43 (PA9)
unnamed: R6.1, U1.44 (PA10)
unnamed: R25.1, U1.45 (PA11)
unnamed: R20.1, U1.46 (PA12)
unnamed: R18.1, U1.26 (PB2)
unnamed: R5.1, U1.57 (PB4)
unnamed: R7.2, U1.58 (PB5)
unnamed: R8.2, U1.59 (PB6)
unnamed: R11.2, U1.60 (PB7)
unnamed: R29.2, TP4.1, U1.34 (PB12)
unnamed: R31.2, TP5.1, U1.35 (PB13)
unnamed: R14.1, TP6.1, U1.36 (PB14)
unnamed: R16.2, TP8.1, U1.37 (PB15)
unnamed: R1.1, U1.22 (PC4)
unnamed: R2.1, U1.23 (PC5)
unnamed: R21.1, U1.38 (PC6)
unnamed: R23.2, U1.39 (PC7)
unnamed: R19.1, U1.54 (PC12)
unnamed: C9.1, C10.1, C11.1, C12.1, FB1.2, U1.28 (VREF+), U1.29 (VDDA)
